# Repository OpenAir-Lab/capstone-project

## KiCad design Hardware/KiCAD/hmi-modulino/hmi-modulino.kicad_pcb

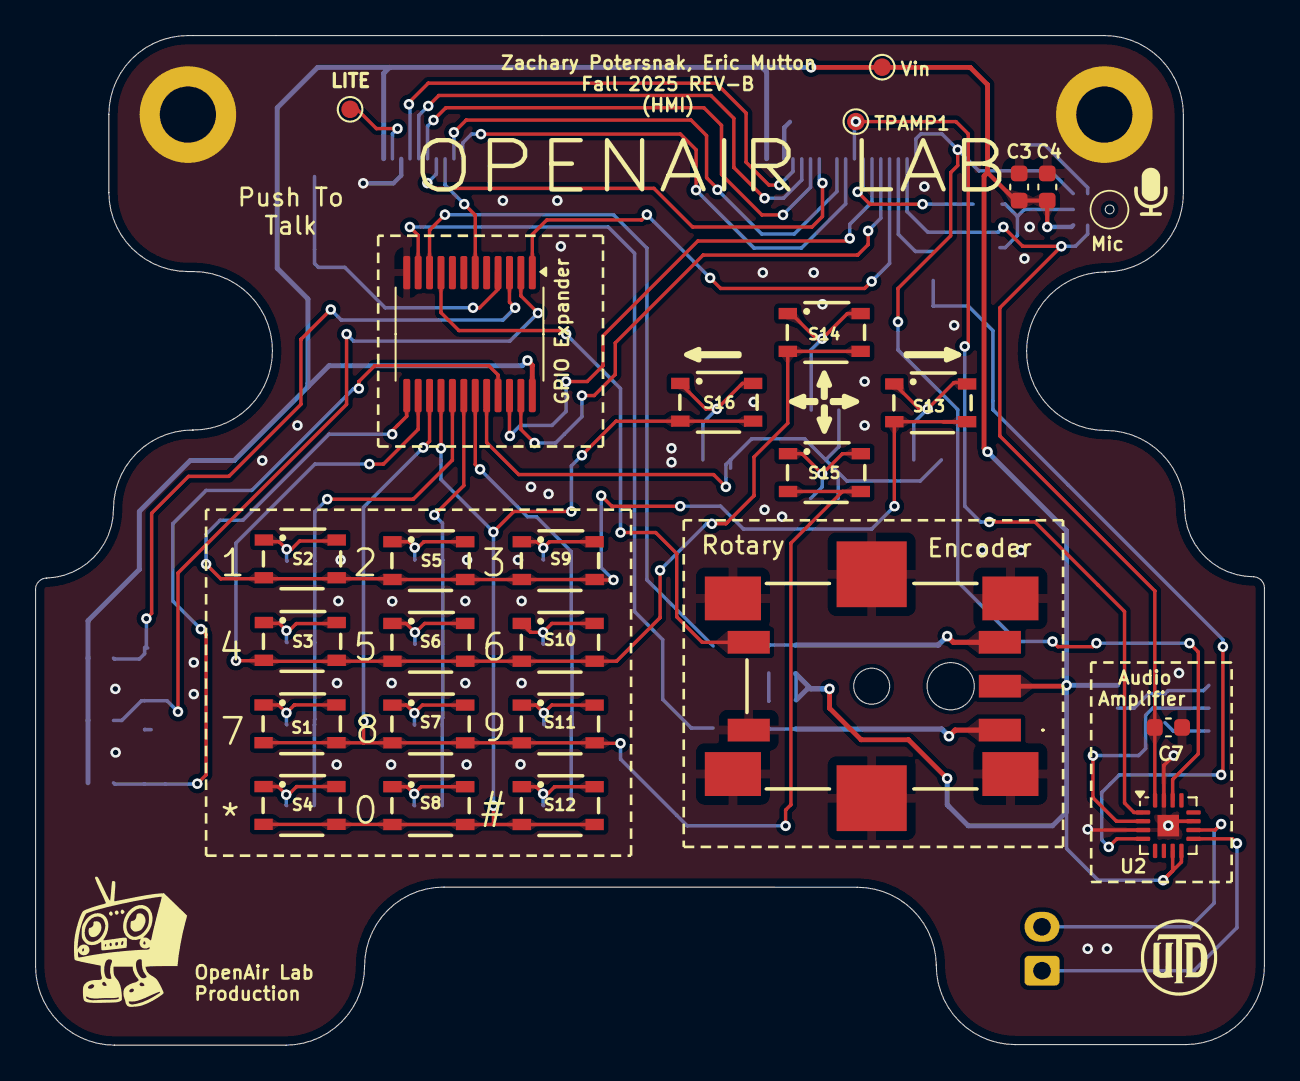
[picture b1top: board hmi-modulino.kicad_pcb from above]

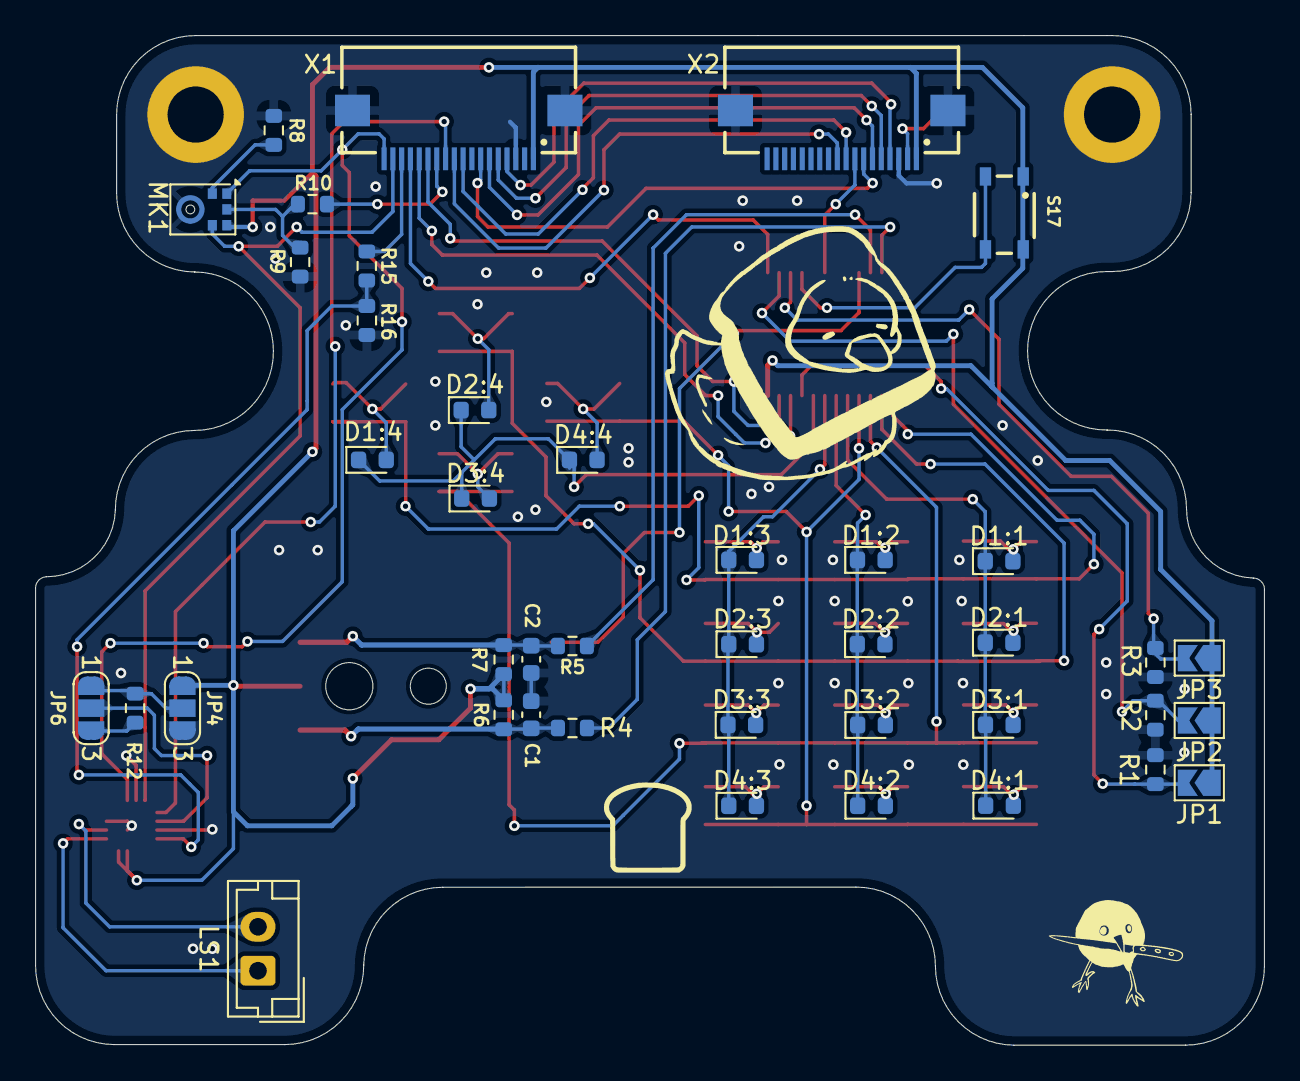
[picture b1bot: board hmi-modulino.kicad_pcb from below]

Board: 2 copper layers, 70.0 x 57.5 mm, 68 parts (41 on the bottom side), 58 nets.

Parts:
C1, C2: 0.01uF; C_0603_1608Metric
C3: 1uF; C_0603_1608Metric
C4: 0.1uF; C_0603_1608Metric
C7: 22pF; C_0603_1608Metric
D1:1, D1:2, D1:3, D1:4, D2:1, D2:2, D2:3, D2:4, D3:1, D3:2, D3:3, D3:4, D4:1, D4:2, D4:3, D4:4: D; D_0603_1608Metric
H1, H2: M3; MountingHole_3.2mm_M3_ISO14580_Pad
IC1: PCF8575PWR; SSOP-24_5.3x8.2mm_P0.65mm
JP1, JP2, JP3: SolderJumper_2_Open; SolderJumper-2_P1.3mm_Open_TrianglePad1.0x1.5mm
JP4: GAIN_{LOGIC}; SolderJumper-3_P1.3mm_Open_RoundedPad1.0x1.5mm_NumberLabels
JP6: GAIN_{R}; SolderJumper-3_P1.3mm_Open_RoundedPad1.0x1.5mm_NumberLabels
LS1: Speaker; JST_EH_B2B-EH-A_1x02_P2.50mm_Vertical
MK1: ICS-43434; InvenSense_ICS-43434-6_3.5x2.65mm
R1, R2, R3, R4, R5, R6, R7: 10k; R_0603_1608Metric
R8, R9: 47k; R_0603_1608Metric
R10: 68; R_0603_1608Metric
R12: 100k 5%; R_0603_1608Metric
R15: 2k; R_0603_1608Metric
R16: 100k; R_0603_1608Metric
S1, S2, S3, S4, S5, S6, S7, S8, S9, S10, S11, S12, S13, S14, S15, S16, S17: 434133025816
TP1: TestPoint; TestPoint_Pad_D1.0mm
TPAMP1: TestPoint_Pad_D1.0mm
U1: PEC11J-9215F-S0015; PEC11J9215FS0015
U2: MAX98357A; TQFN-16-1EP_3x3mm_P0.5mm_EP1.23x1.23mm
Vin: TestPoint; TestPoint_Pad_D1.0mm
X1, X2: EYESPI; Adafruit EYESPI FPC Connector

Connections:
+3.3V: C3.1, C4.1, IC1.24 (VCC), JP1.1 (A), JP2.1 (A), JP3.1 (A), JP4.1 (A), MK1.5 (VDD), R6.1, R7.2, S17.1, S17.2, U1.C1, U2.7 (VDD), U2.8 (VDD), Vin.1, X1.1, X2.1
/CARDCS: X1.10, X2.10
/Human-Machine Interface/AMP_DIN: TPAMP1.1, U2.1 (DIN), X1.11
/Human-Machine Interface/Audio/GAIN_SLOT: JP6.2 (C), U2.2 (GAIN_SLOT)
/Human-Machine Interface/Audio/~SD_MODE: R15.1, R16.2, U2.4 (~SD_MODE)
/Human-Machine Interface/BCLK: C7.1, MK1.4 (SCK), U2.16 (BCLK), X1.17
/Human-Machine Interface/ENC_CLK: IC1.11 (P7), R4.1
/Human-Machine Interface/ENC_DT: IC1.10 (P6), R5.1
/Human-Machine Interface/ENC_SW: IC1.9 (P5), U1.E1 (NO)
/Human-Machine Interface/Keypad/COL1: D1:1.1 (K), D2:1.1 (K), D3:1.1 (K), D4:1.1 (K), IC1.17 (P14)
/Human-Machine Interface/Keypad/COL2: D1:2.1 (K), D2:2.1 (K), D3:2.1 (K), D4:2.1 (K), IC1.18 (P15)
/Human-Machine Interface/Keypad/COL3: D1:3.1 (K), D2:3.1 (K), D3:3.1 (K), D4:3.1 (K), IC1.19 (P16)
/Human-Machine Interface/Keypad/COL4: D1:4.1 (K), D2:4.1 (K), D3:4.1 (K), D4:4.1 (K), IC1.20 (P17)
/Human-Machine Interface/Keypad/ROW1: IC1.13 (P10), S2.3, S2.4, S5.3, S5.4, S9.3, S9.4, S13.3, S13.4
/Human-Machine Interface/Keypad/ROW2: IC1.14 (P11), S3.3, S3.4, S6.3, S6.4, S10.3, S10.4, S14.3, S14.4
/Human-Machine Interface/Keypad/ROW3: IC1.15 (P12), S1.3, S1.4, S7.3, S7.4, S11.3, S11.4, S15.3, S15.4
/Human-Machine Interface/Keypad/ROW4: IC1.16 (P13), S4.3, S4.4, S8.3, S8.4, S12.3, S12.4, S16.3, S16.4
/Human-Machine Interface/LITE: TP1.1, X2.2
/Human-Machine Interface/LRCLK: MK1.1 (WS), U2.14 (LRCLK), X1.18
/Human-Machine Interface/MIC_DOUT: R10.2, X1.12
/Human-Machine Interface/PCF_A0: IC1.21 (A0), JP1.2 (B), R1.1
/Human-Machine Interface/PCF_A1: IC1.2 (A1), JP2.2 (B), R2.1
/Human-Machine Interface/PCF_A2: IC1.3 (A2), JP3.2 (B), R3.1
/Human-Machine Interface/TFTRST: IC1.6 (P2), X2.8
/Human-Machine Interface/~AMP_SD: R15.2, X1.16
/MISO: X1.6, X2.6
/MOSI: X1.5, X2.5
/SCK: X1.4, X2.4
/SCL: IC1.22 (SCL), X1.13
/SDA: IC1.23 (SDA), X1.14
/TFTCS: X1.9, X2.9
/TFTDC: X1.7, X2.7
GND: C1.2, C2.2, C3.2, C4.2, C7.2, H1.1, H2.1, IC1.12 (GND), JP4.3 (B), MK1.3 (GND), R1.2, R2.2, R3.2, R8.2, R9.2, R16.1, U1.D1 (COM), U1.MP1, U1.MP2, U1.MP3, U1.MP4, U1.MP5, U1.MP6, U2.3 (GND), U2.11 (GND), U2.15 (GND), U2.17 (PAD), X1.3, X1.Z1, X1.Z2, X2.3, X2.Z1, X2.Z2
unnamed: C1.1, R4.2, R6.2, U1.A1
unnamed: C2.1, R5.2, R7.1, U1.B1
unnamed: D1:1.2 (A), S2.1, S2.2
unnamed: D1:2.2 (A), S5.1, S5.2
unnamed: D1:3.2 (A), S9.1, S9.2
unnamed: D1:4.2 (A), S13.1, S13.2
unnamed: D2:1.2 (A), S3.1, S3.2
unnamed: D2:2.2 (A), S6.1, S6.2
unnamed: D2:3.2 (A), S10.1, S10.2
unnamed: D2:4.2 (A), S14.1, S14.2
unnamed: D3:1.2 (A), S1.1, S1.2
unnamed: D3:2.2 (A), S7.1, S7.2
unnamed: D3:3.2 (A), S11.1, S11.2
unnamed: D3:4.2 (A), S15.1, S15.2
unnamed: D4:1.2 (A), S4.1, S4.2
unnamed: D4:2.2 (A), S8.1, S8.2
unnamed: D4:3.2 (A), S12.1, S12.2
unnamed: D4:4.2 (A), S16.1, S16.2
unnamed: IC1.4 (P0), S17.3, S17.4
unnamed: JP4.2 (C), JP6.1 (A), R12.1
unnamed: JP6.3 (B), R12.2
unnamed: MK1.2 (LR), R8.1
unnamed: MK1.6 (SD), R9.1, R10.1
unnamed: LS1.2, U2.10 (OUTN)
unnamed: LS1.1, U2.9 (OUTP)

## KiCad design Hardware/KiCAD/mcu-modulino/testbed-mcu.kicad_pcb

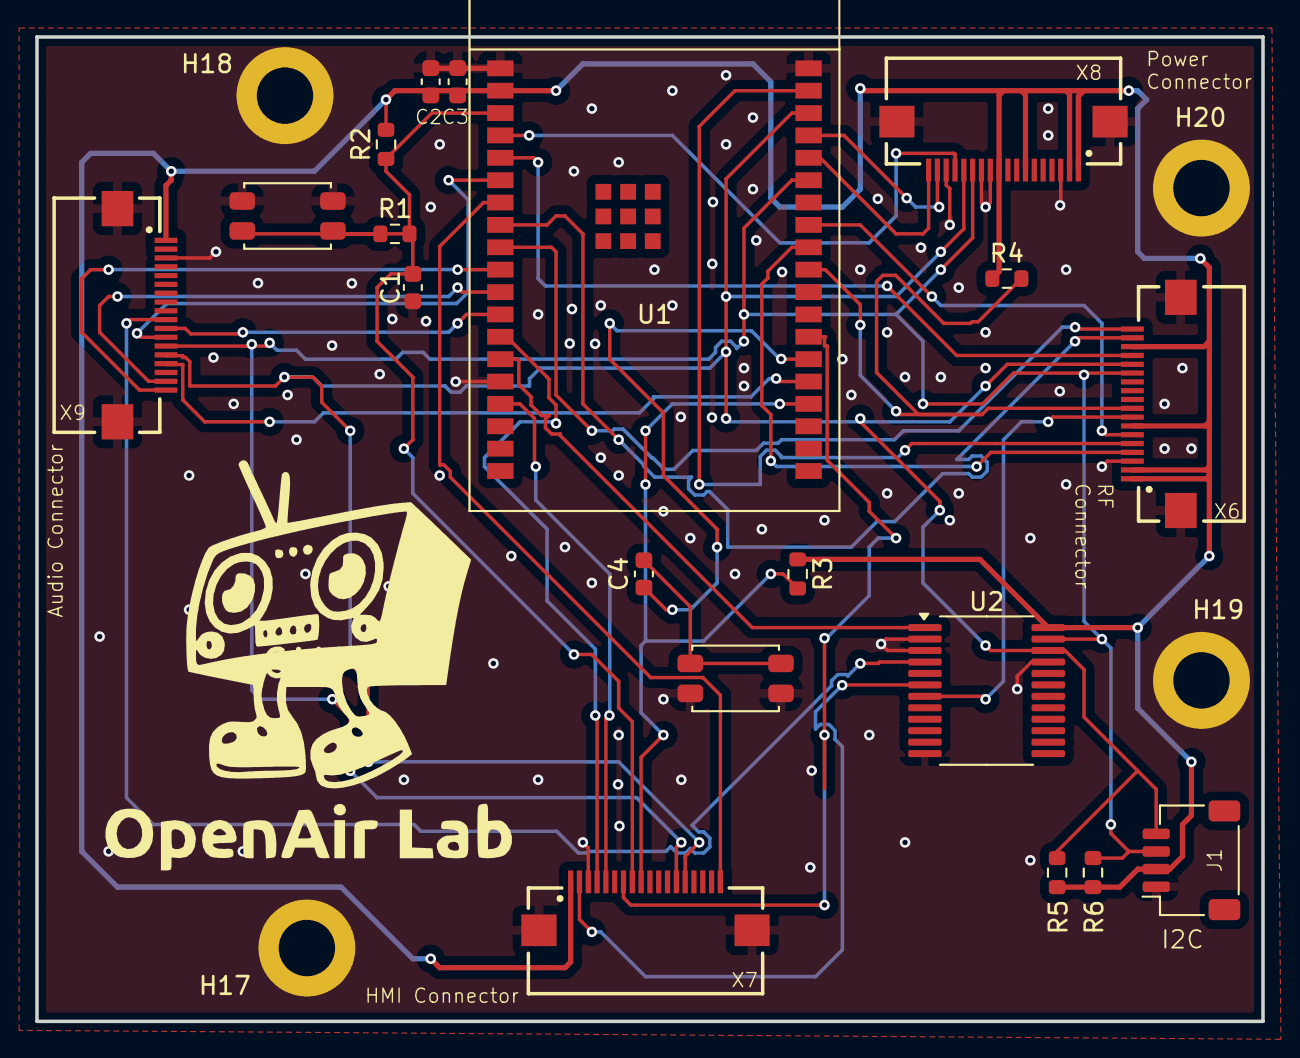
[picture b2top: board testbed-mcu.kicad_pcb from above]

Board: 2 copper layers, 69.6 x 55.9 mm, 23 parts (0 on the bottom side), 31 nets.

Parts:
C1, C3, C4: 0.1u; C_0603_1608Metric
C2: 10u; C_0603_1608Metric
H17, H18, H19, H20: MountingHole_Pad; MountingHole_3.2mm_M3_ISO14580_Pad
J1: Stemma QT; JST_SH_SM04B-SRSS-TB_1x04-1MP_P1.00mm_Horizontal
R1, R2, R3, R4: 10k; R_0603_1608Metric
R5, R6: 4.7k; R_0603_1608Metric
SW1, SW2: SW_Push; SW_SPST_EVQP2_MiddlePushTravel_H2.5mm
U1: ESP32-WROVER-E; ESP32-WROVER-IE
U2: PCF8575DBR; SSOP-24_5.3x8.2mm_P0.65mm
X6, X7, X8, X9: EYESPI; Adafruit EYESPI FPC Connector

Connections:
+3.3V: C2.2, C3.2, J1.2, R2.2, R3.1, R4.1, R5.1, R6.1, U1.2 (3V3), U2.24 (VCC), X6.1, X6.2, X6.7, X6.16, X7.1, X8.1, X8.2, X8.7, X8.10, X9.1
/AMP_SD: U2.4 (P0), X9.10
/CC1200_RST: U2.7 (P3), X6.8
/MCU/AUDIO_INT: U1.24 (IO2), X9.15
/MCU/BCLK: U1.11 (GPIO26), X9.17
/MCU/BMS_INT: U1.4 (GPIO36), X8.15
/MCU/DIN: U1.6 (GPIO34), X9.12
/MCU/DOUT: U1.12 (GPIO27), X9.11
/MCU/HMI_INT: U1.7 (GPIO35), X7.18
/MCU/HSPI_CS: R3.2, U1.23 (IO15), X7.9
/MCU/HSPI_DC: U1.26 (GPIO4), X7.7
/MCU/HSPI_MOSI: U1.16 (GPIO13), X7.5
/MCU/HSPI_SCLK: U1.13 (GPIO14), X7.4
/MCU/LRCLK: U1.10 (GPIO25), X9.18
/MCU/RF_INT: U1.5 (GPIO39), X6.15
/MCU/RX0: U1.34 (RXD0), X8.18
/MCU/TX0: U1.35 (TXD0), X8.17
/MCU/VSPI_CS: R4.2, U1.29 (IO5), X6.9
/MCU/VSPI_GDO0: U1.8 (GPIO32), X6.17
/MCU/VSPI_GDO2: U1.9 (GPIO33), X6.18
/MCU/VSPI_MISO: U1.31 (GPIO19), X6.6
/MCU/VSPI_MOSI: U1.37 (GPIO23), X6.5
/MCU/VSPI_SCLK: U1.30 (GPIO18), X6.4
/MCU/X_INT: U1.14 (IO12), U2.1 (~INT)
/TFT_BL_EN: U2.6 (P2), X7.2
EN: C1.2, R1.1, R1.2, R2.1, SW1.2, U1.3 (EN), X7.8
GND: C1.1, C2.1, C3.1, H17.1, H18.1, H19.1, H20.1, J1.1, SW1.1, SW2.2, U1.1 (GND), U1.15 (GND), U1.38 (GND), U2.2 (A1), U2.3 (A2), U2.12 (GND), U2.21 (A0), X6.3, X6.Z1, X6.Z2, X7.3, X7.Z1, X7.Z2, X8.3, X8.11, X8.12, X8.16, X8.Z1, X8.Z2, X9.3, X9.Z1, X9.Z2
unnamed: C4.2, SW2.1
unnamed: C4.1, U1.25 (IO0)
SCL: J1.4, R5.2, U1.36 (GPIO22), U2.22 (SCL), X6.14, X7.14, X8.14, X9.14
SDA: J1.3, R6.2, U1.33 (GPIO21), U2.23 (SDA), X6.13, X7.13, X8.13, X9.13

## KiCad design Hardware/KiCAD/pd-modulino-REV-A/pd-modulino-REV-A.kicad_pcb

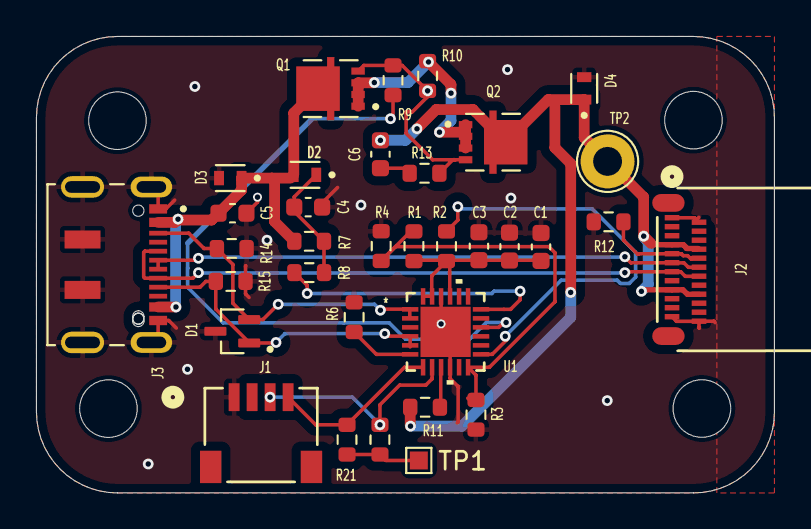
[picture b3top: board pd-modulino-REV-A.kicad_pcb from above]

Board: 2 copper layers, 41.0 x 25.4 mm, 34 parts (0 on the bottom side), 21 nets.

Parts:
C1, C2, C3, C4: 1.0u; C_0603_1608Metric
C5: 4.7u; C_0603_1608Metric
C6: 100n; C_0603_1608Metric
D1: ESDA25W; SOT65P210X110-3N
D2, D3, D4: ESDA25P35-1U1M; TVS_ESDA25P35-1U1M
J1: PRT-14417; CONN_PRT-14417_SPK
J2: USB4155-03-C; CONN_USB4155_GCT
J3: DX07S016JA1R1500; JAE_DX07S016JA1R1500
Q1, Q2: STL6P3LLH6; TRANS_STL6P3LLH6
R1, R2, R6: 10k; R_0603_1608Metric
R3, R4, R10: 100k; R_0603_1608Metric
R5, R21: 4.7k; R_0603_1608Metric
R7: 470; R_0603_1608Metric
R8, R11: 1k; R_0603_1608Metric
R9: 22k; R_0603_1608Metric
R12, R14, R15: 5.1k; R_0603_1608Metric
R13: 100; R_0603_1608Metric
TP1: TestPoint; TestPoint_Pad_1.0x1.0mm
TP2: TestPoint; TestPoint_Loop_D2.60mm_Drill1.6mm_Beaded
U1: STUSB4500QTR

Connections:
/Power Subsystem/2V7: C1.2, C2.2, C3.2, R1.2, R2.2, U1.21 (VREG_1V2), U1.23 (VREG_2V7), U1.24 (VDD)
/Power Subsystem/D+: J2.A6 (D+), J2.B7 (D+), J3.6 (D+), J3.7 (D+__1)
/Power Subsystem/D-: J2.A7 (D-), J2.B6 (D-), J3.5 (D-), J3.8 (D-__1)
/Power Subsystem/SCL: J1.4, R21.2, U1.7 (SCL)
/Power Subsystem/SDA: J1.3, R5.2, U1.8 (SDA)
/Power Subsystem/USB_CC1: D1.2, J3.3 (CC1), R14.1, U1.1 (CC1DB), U1.2 (CC1)
/Power Subsystem/USB_CC2: D1.1, J3.9 (CC2), R15.1, U1.4 (CC2), U1.5 (CC2DB)
/Power Subsystem/VBUS_VS_DISCH: R8.1, U1.18 (VBUS_VS_DISCH)
GND: C1.1, C2.1, C3.1, C4.2, C5.2, D1.3, D3.A, D4.A, J1.1, J2.A1 (GND), J2.A12 (GND), J2.B1 (GND), J2.B12 (GND), J3.1 (GND), J3.12 (GND__1), J3.S1 (SHIELD), J3.S2 (SHIELD__1), J3.S3 (SHIELD__2), J3.S4 (SHIELD__3), J3.S5 (SHIELD__4), J3.S6 (SHIELD__5), R3.1, R4.1, R6.1, R12.1, R14.2, R15.2, U1.10 (GND), U1.22 (VSYS), U1.25
unnamed: C4.1, D2.C, R7.1, R8.2
unnamed: C6.1, R13.1
unnamed: J2.A5 (CC1), J2.B8 (CC2), R12.2
unnamed: Q1.1, Q1.2, Q1.3, Q2.1, Q2.2, Q2.3, R10.2
unnamed: Q1.4, Q2.4, R9.2, R10.1, R13.2
unnamed: R5.1, R21.1, TP1.1
unnamed: R1.1, R3.2, R4.2, U1.12 (ADDR0)
unnamed: R2.1, U1.13 (ADDR1)
unnamed: R11.2, U1.9 (DISCH)
unnamed: R6.2, U1.6 (RESET)
unnamed: R9.1, U1.16 (VBUS_EN_SNK)
VBUS: C5.1, C6.2, D2.A, D3.C, D4.C, J2.A4 (VDD), J2.A9 (VDD), J2.B4 (VDD), J2.B9 (VDD), J3.2 (VBUS), J3.11 (VBUS__1), Q1.5_8, Q2.5_8, R7.2, R11.1, TP2.1

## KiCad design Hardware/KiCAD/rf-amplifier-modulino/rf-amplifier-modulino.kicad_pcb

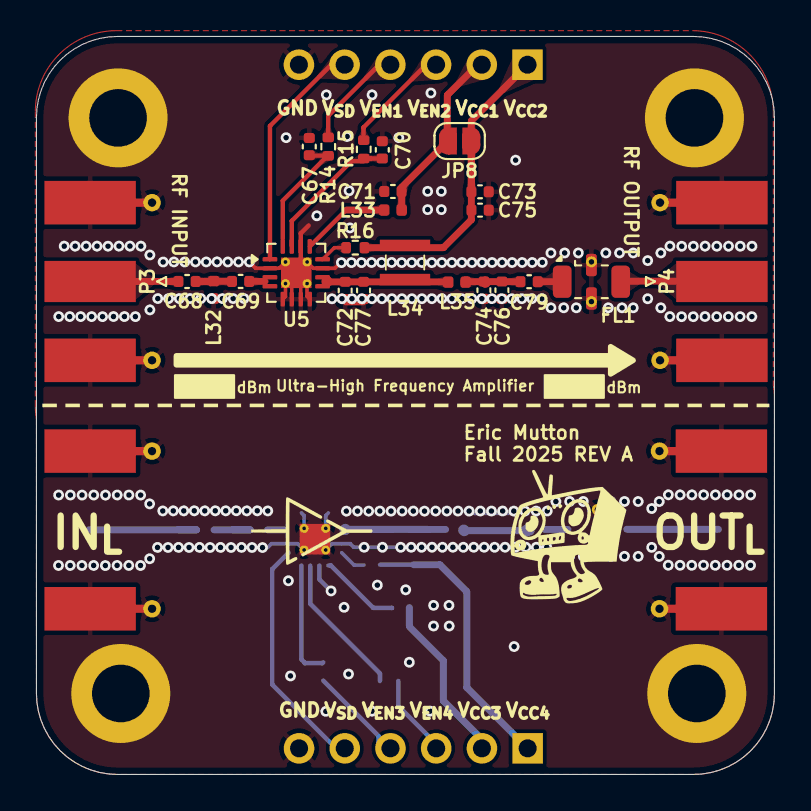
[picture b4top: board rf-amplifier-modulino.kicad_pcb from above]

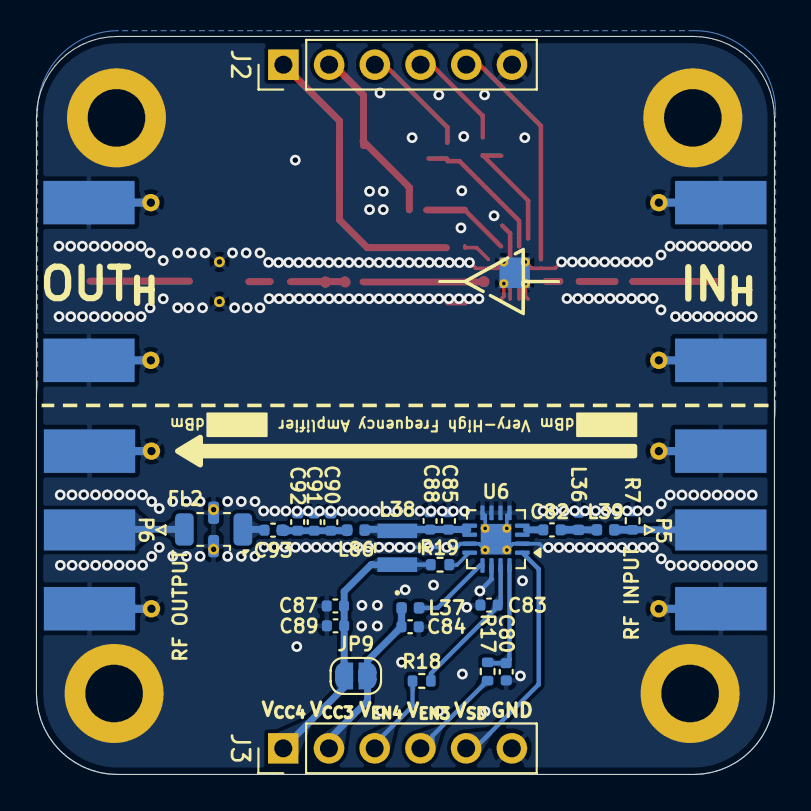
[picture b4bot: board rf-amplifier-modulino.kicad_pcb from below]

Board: 4 copper layers, 41.0 x 41.0 mm, 56 parts (28 on the bottom side), 32 nets.

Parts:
C67, C70, C75, C80, C83, C89: 1nF; C_0402_1005Metric
C68: 10pF; C_0402_1005Metric
C69, C72: 33pF; C_0402_1005Metric
C71: 0.1uF; C_0402_1005Metric
C73, C87: 10uF; C_0402_1005Metric
C74: 27pF; C_0402_1005Metric
C76: 3pF; C_0402_1005Metric
C77: 6.8pF; C_0402_1005Metric
C79, C88: 100pF; C_0402_1005Metric
C82, C93: 220pF; C_0402_1005Metric
C84: 1uF; C_0402_1005Metric
C85: 270pF; C_0402_1005Metric
C90, C91: 47pF; C_0402_1005Metric
C92: 18pF; C_0402_1005Metric
FL1: LFCN-490; Filter_Mini-Circuits_FV1206
FL2: LFCN-160; Filter_Mini-Circuits_FV1206
H1, H3, H4, H8: M3; MountingHole_3.2mm_M3_ISO14580_Pad
J2, J3: Conn_01x06_Pin; PinHeader_1x06_P2.54mm_Vertical
JP8, JP9: Single V_{CC}; SolderJumper-2_P1.3mm_Open_RoundedPad1.0x1.5mm
L32: 10nH; L_0402_1005Metric
L33: 20nH; L_0402_1005Metric
L34: 23nH; 0908SQ23NGLC
L35: 2.4nH; L_0402_1005Metric
L36: 150nH; L_0402_1005Metric
L37: 56nH; L_0402_1005Metric
L38: 1uH; IND_IMSC1008AZER_VIS
L39: 68nH; L_0402_1005Metric
L86: 9.1nH; L_0402_1005Metric
P3, P4, P5, P6: SMA; SMA_Molex_73251-1153_EdgeMount_Horizontal
R7: 350; R_0402_1005Metric
R14, R17: 1.27k; R_0402_1005Metric
R15, R18: 3.0k; R_0402_1005Metric
R16, R19: 0k; R_0402_1005Metric
U5, U6: GRF5604; QFN-16-1EP_3x3mm_P0.5mm_EP1.7x1.7mm_ThermalVias

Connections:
+3.3V: C71.1, C84.1, J2.2, J3.2, JP8.1 (A), JP9.1 (A), L33.1, L37.1
/RF Subsystem/RF Frontend/UHF 6W PA/RF_{IN}: C68.1, P3.1 (In)
/RF Subsystem/RF Frontend/UHF 6W PA/RF_{OUT}: C79.2, FL1.1 (IN)
/RF Subsystem/RF Frontend/UHF 6W PA/V_{CC2}: C73.1, C75.1, J2.1, JP8.2 (B), L34.1, R16.2
/RF Subsystem/RF Frontend/UHF 6W PA/V_{EN1}: C67.1, R14.1, U5.16 (V_{ENABLE1})
/RF Subsystem/RF Frontend/UHF 6W PA/V_{EN2}: C70.1, R15.1, U5.15 (V_{ENABLE2})
/RF Subsystem/RF Frontend/UHF 6W PA/V_{ENABLE1}: J2.4, R14.2
/RF Subsystem/RF Frontend/UHF 6W PA/V_{ENABLE2}: J2.3, R15.2
/RF Subsystem/RF Frontend/UHF 6W PA/V_{SHUTDOWN}: J2.5, U5.1 (V_{SHUTDOWN})
/RF Subsystem/RF Frontend/VHF 6W PA/RF_{IN}: L39.1, P5.1 (In), R7.2
/RF Subsystem/RF Frontend/VHF 6W PA/RF_{OUT}: C93.2, FL2.1 (IN)
/RF Subsystem/RF Frontend/VHF 6W PA/V_{CC2}: C87.1, C89.1, J3.1, JP9.2 (B), L38.1, R19.2
/RF Subsystem/RF Frontend/VHF 6W PA/V_{EN1}: C80.1, R17.1, U6.16 (V_{ENABLE1})
/RF Subsystem/RF Frontend/VHF 6W PA/V_{EN2}: C83.1, R18.1, U6.15 (V_{ENABLE2})
/RF Subsystem/RF Frontend/VHF 6W PA/V_{ENABLE1}: J3.4, R17.2
/RF Subsystem/RF Frontend/VHF 6W PA/V_{ENABLE2}: J3.3, R18.2
/RF Subsystem/RF Frontend/VHF 6W PA/V_{SHUTDOWN}: J3.5, U6.1 (V_{SHUTDOWN})
GND: C67.2, C70.2, C71.2, C72.2, C73.2, C74.2, C75.2, C76.2, C77.2, C80.2, C83.2, C84.2, C85.2, C87.2, C88.2, C89.2, C90.2, C91.2, C92.2, FL1.2 (GND), FL1.4 (GND), FL2.2 (GND), FL2.4 (GND), H1.1, H3.1, H4.1, H8.1, J2.6, J3.6, L32.2, L36.2, P3.2 (Ext), P4.2 (Ext), P5.2 (Ext), P6.2 (Ext), R7.1, U5.2 (GND/NC), U5.5 (GND/NC), U5.6 (GND/NC), U5.7 (GND/NC), U5.8 (GND/NC), U5.11 (GND/NC), U5.14 (GND/NC), U5.17 (PAD), U6.2 (GND/NC), U6.5 (GND/NC), U6.6 (GND/NC), U6.7 (GND/NC), U6.8 (GND/NC), U6.11 (GND/NC), U6.14 (GND/NC), U6.17 (PAD)
unnamed: C68.2, C69.1, L32.1
unnamed: C69.2, U5.3 (RF_{IN}), U5.4 (RF_{IN})
unnamed: C72.1, C77.1, L34.2, L35.1, U5.9 (RF_{OUT}), U5.10 (RF_{OUT})
unnamed: C74.1, C76.1, C79.1, L35.2
unnamed: C82.1, L36.1, L39.2
unnamed: C82.2, U6.3 (RF_{IN}), U6.4 (RF_{IN})
unnamed: C85.1, C88.1, L38.2, L86.1, U6.9 (RF_{OUT}), U6.10 (RF_{OUT})
unnamed: C90.1, C91.1, C92.1, C93.1, L86.2
unnamed: FL1.3 (OUT), P4.1 (In)
unnamed: FL2.3 (OUT), P6.1 (In)
unnamed: R16.1, U5.12 (V_{BIAS})
unnamed: L33.2, U5.13 (V_{CC1})
unnamed: R19.1, U6.12 (V_{BIAS})
unnamed: L37.2, U6.13 (V_{CC1})

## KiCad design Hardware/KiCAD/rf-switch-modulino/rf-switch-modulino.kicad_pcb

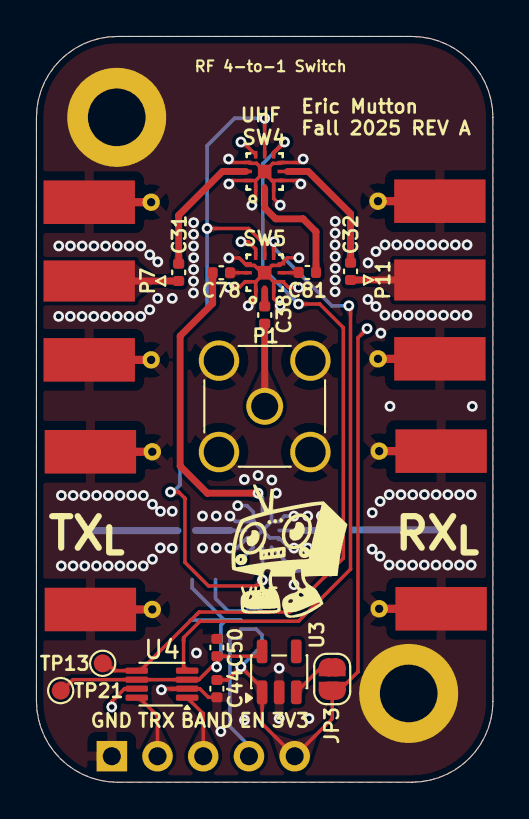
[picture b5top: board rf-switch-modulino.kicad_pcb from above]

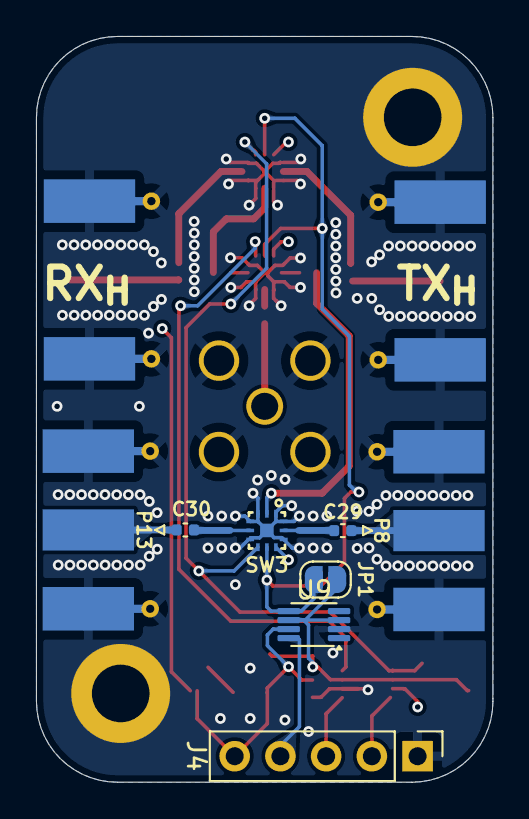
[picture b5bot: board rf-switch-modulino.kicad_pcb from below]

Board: 4 copper layers, 25.4 x 41.4 mm, 27 parts (8 on the bottom side), 24 nets.

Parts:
C29, C30, C31, C32, C78, C81: 1nF; C_0402_1005Metric
C38: 100pF; C_0402_1005Metric
C44, C50: 1uF; C_0402_1005Metric
H5, H6: M3; MountingHole_3.2mm_M3_ISO14580_Pad
J4: RF Switch; PinHeader_1x05_P2.54mm_Vertical
JP1, JP3: EN; SolderJumper-2_P1.3mm_Open_RoundedPad1.0x1.5mm
P1: SMA; SMA_Amphenol_901-144_Vertical
P7, P8, P11, P13: SMA; SMA_Molex_73251-1153_EdgeMount_Horizontal
SW3, SW4, SW5: SKY13330-397LF
TP13: TRX_SW_{+2.5V}; TestPoint_Pad_D1.0mm
TP21: +2.5V; TestPoint_Pad_D1.0mm
U3: LP5907MFX-2.5; SOT-23-5
U4, U9: TXS0101DBV; VSSOP-8_2.3x2mm_P0.5mm

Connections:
+2.5V: C50.2, JP1.1 (A), TP21.1, U3.5 (OUT), U4.3 (VCCA), U4.6 (OE), U9.3 (VCCA), U9.6 (OE)
+3.3V: C44.2, J4.5, JP3.1 (A), SW3.9 (VDD), SW4.9 (VDD), SW5.9 (VDD), U3.1 (IN), U4.7 (VCCB), U9.7 (VCCB)
/RF Subsystem/EN_{BAND}: JP1.2 (B), SW3.8 (EN), SW4.8 (EN), SW5.8 (EN), U9.5 (A1)
/RF Subsystem/RF Frontend/RX_{UHF}: C32.1, P11.1 (In)
/RF Subsystem/RF Frontend/RX_{VHF}: C30.1, P13.1 (In)
/RF Subsystem/RF Frontend/TX_{UHF}: C31.1, P7.1 (In)
/RF Subsystem/RF Frontend/TX_{VHF}: C29.1, P8.1 (In)
/RF Subsystem/RFSW_{BAND}: J4.3, U4.1 (B2)
/RF Subsystem/RFSW_{EN}: J4.4, U9.8 (B1)
/RF Subsystem/RFSW_{TRX}: J4.2, U4.8 (B1)
/RF Subsystem/SW_BAND: SW5.7 (CTRL), U4.4 (A2)
/RF Subsystem/SW_TRX: SW3.7 (CTRL), SW4.7 (CTRL), TP13.1, U4.5 (A1)
GND: C44.1, C50.1, H5.1, H6.1, J4.1, P1.2 (Ext), P7.2 (Ext), P8.2 (Ext), P11.2 (Ext), P13.2 (Ext), SW3.1 (GND), SW3.3 (GND), SW3.4 (GND), SW3.6 (GND), SW3.10 (GND), SW3.12 (GND), SW3.13 (GND), SW4.1 (GND), SW4.3 (GND), SW4.4 (GND), SW4.6 (GND), SW4.10 (GND), SW4.12 (GND), SW4.13 (GND), SW5.1 (GND), SW5.3 (GND), SW5.4 (GND), SW5.6 (GND), SW5.10 (GND), SW5.12 (GND), SW5.13 (GND), U3.2 (GND), U4.2 (GND), U9.2 (GND)
unnamed: JP3.2 (B), U3.3 (EN)
unnamed: C38.1, P1.1 (In)
unnamed: C78.1, SW3.2 (RF1_COM)
unnamed: C29.2, SW3.11 (RF2)
unnamed: C30.2, SW3.5 (RF3)
unnamed: C81.1, SW4.2 (RF1_COM)
unnamed: C31.2, SW4.11 (RF2)
unnamed: C32.2, SW4.5 (RF3)
unnamed: C38.2, SW5.2 (RF1_COM)
unnamed: C78.2, SW5.11 (RF2)
unnamed: C81.2, SW5.5 (RF3)

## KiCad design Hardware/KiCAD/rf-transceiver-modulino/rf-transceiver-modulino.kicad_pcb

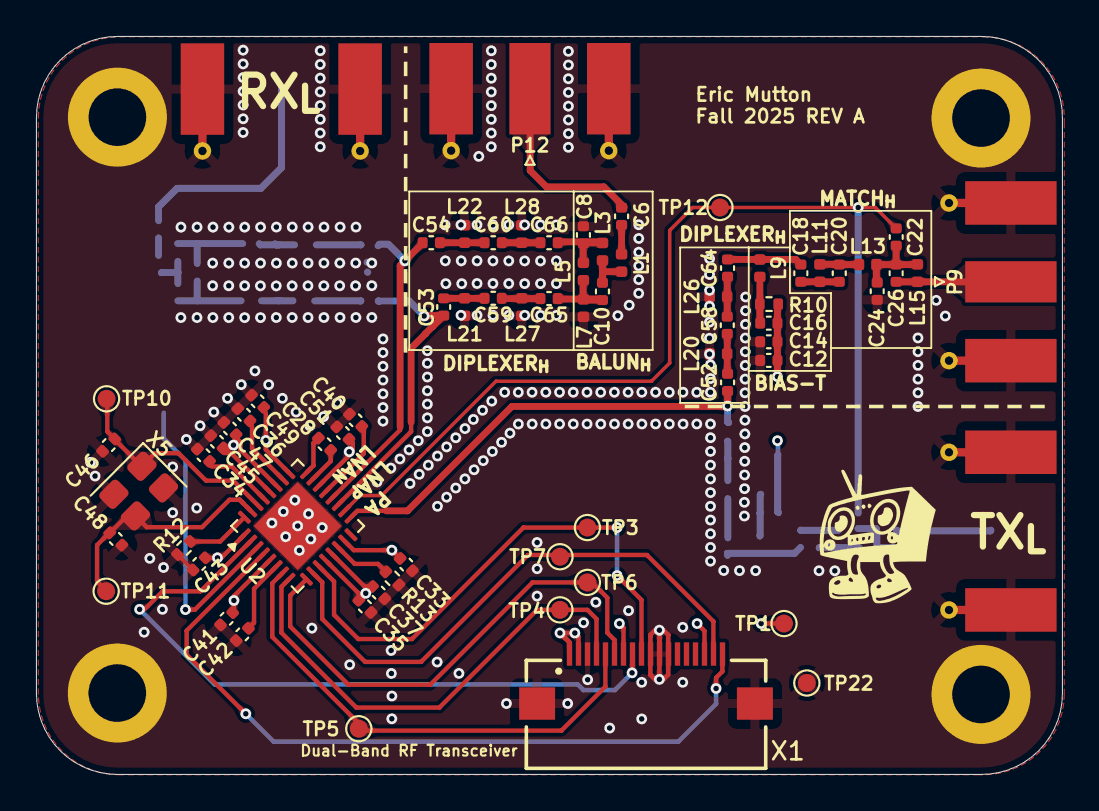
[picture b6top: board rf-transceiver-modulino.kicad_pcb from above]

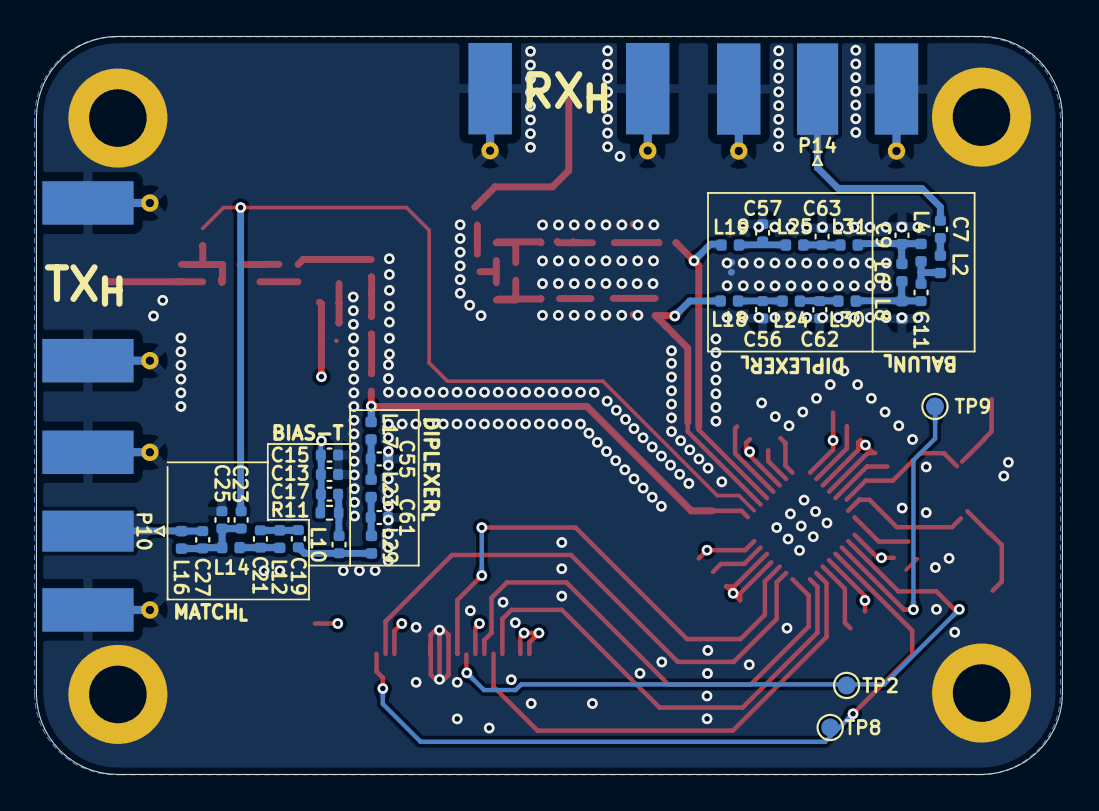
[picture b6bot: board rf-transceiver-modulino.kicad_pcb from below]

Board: 4 copper layers, 57.0 x 41.0 mm, 112 parts (40 on the bottom side), 58 nets.

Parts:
C6, C8, C10: 5.1pF; C_0402_1005Metric
C7, C9, C11, C21, C23: 12pF; C_0402_1005Metric
C12: 100p; C_0402_1005Metric
C13, C17: 100pF; C_0402_1005Metric
C14, C40: 10n; C_0402_1005Metric
C15: 10nF; C_0402_1005Metric
C16: 56p; C_0402_1005Metric
C18: 39p; C_0402_1005Metric
C19: 82pF; C_0402_1005Metric
C20: 2.2p; C_0402_1005Metric
C22: 1nF; C_0402_1005Metric
C24: 6.2p; C_0402_1005Metric
C25: 15pF; C_0402_1005Metric
C26, C27: 1.2p; C_0402_1005Metric
C28: 1.5n; C_0402_1005Metric
C33, C34, C35, C36, C37, C41, C43, C45, C47, C49, C51: 47n; C_0402_1005Metric
C42: 220n; C_0402_1005Metric
C46, C48: 15p; C_0402_1005Metric
C52, C53, C54, C64, C65, C66: 4.7pF; C_0402_1005Metric
C55, C56, C57, C61, C62, C63: 18pF; C_0402_1005Metric
C58, C59, C60: 2.7pF; C_0402_1005Metric
H1, H2, H3, H5: M3; MountingHole_3.2mm_M3_ISO14580_Pad
L1, L20, L21, L22, L26, L27, L28: 15nH; L_0402_1005Metric
L2: 39nH; L_0402_1005Metric
L3, L7: 27nH; L_0402_1005Metric
L4, L8: 82nH; L_0402_1005Metric
L5, L9: 56n; L_0402_1005Metric
L6: 150n; L_0402_1005Metric
L10: 220nH; C_0402_1005Metric
L11: 15n; L_0402_1005Metric
L12: 18nH; L_0402_1005Metric
L13: 43n; L_0402_1005Metric
L14, L23, L24, L25: 100nH; L_0402_1005Metric
L15: 22n; L_0402_1005Metric
L16, L17, L18, L19, L29, L30, L31: 68nH; L_0402_1005Metric
P9, P10, P12, P14: SMA; SMA_Molex_73251-1153_EdgeMount_Horizontal
R10: 18; R_0402_1005Metric
R11: 22; R_0402_1005Metric
R12: 0R; R_0402_1005Metric
R13: 56k; R_0402_1005Metric
TP1: +3.3V; TestPoint_Pad_D1.0mm
TP2: NRST; TestPoint_Pad_D1.0mm
TP3: NCS; TestPoint_Pad_D1.0mm
TP4: SCLK; TestPoint_Pad_D1.0mm
TP5: MOSI; TestPoint_Pad_D1.0mm
TP6: IO1/MISO; TestPoint_Pad_D1.0mm
TP7: IO0; TestPoint_Pad_D1.0mm
TP8: IO2; TestPoint_Pad_D1.0mm
TP9: IO3; TestPoint_Pad_D1.0mm
TP10: X1; TestPoint_Pad_D1.0mm
TP11: X2; TestPoint_Pad_D1.0mm
TP12: TRX_SW; TestPoint_Pad_D1.0mm
TP22: GND; TestPoint_Pad_D1.0mm
U2: CC1200RHBR; QFN-32-1EP_5x5mm_P0.5mm_EP3.45x3.45mm
X1: EYESPI; Adafruit EYESPI FPC Connector
X5: 40 MHz; Crystal_SMD_3225-4Pin_3.2x2.5mm

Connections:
+3.3V: C12.1, C13.1, C14.1, C15.1, C16.1, C17.1, C33.1, C35.1, C37.1, C41.1, C43.1, C45.1, C47.1, C49.1, C51.1, R10.1, R11.1, TP1.1, U2.1 (VDD_GUARD), U2.5 (DVDD), U2.12 (DVDD), U2.13 (AVDD_IF), U2.15 (AVDD_RF), U2.22 (AVDD_SYNTH1), U2.25 (AVDD_PFD_CHP), U2.27 (AVDD_SYNTH2), U2.28 (AVDD_XOSC), X1.1, X1.2, X1.7, X1.16
/RF Subsystem/LNA_N: C54.1, L19.1, U2.20 (LNA_N)
/RF Subsystem/LNA_N_{UHF}: C8.1, C66.2, L3.1, L5.2
/RF Subsystem/LNA_N_{VHF}: C9.1, L4.1, L6.2, L31.2
/RF Subsystem/LNA_P: C53.1, L18.1, U2.19 (LNA_P)
/RF Subsystem/LNA_P_{UHF}: C10.1, C65.2, L5.1, L7.1
/RF Subsystem/LNA_P_{VHF}: C11.1, L6.1, L8.1, L30.1
/RF Subsystem/PA_{SHUTDOWN}: TP9.1, U2.3 (GPIO3)
/RF Subsystem/PA_{UHF}: C18.2, C64.2, L9.2
/RF Subsystem/PA_{VHF}: C19.2, L10.2, L29.2
/RF Subsystem/TRX_GPIO0: TP7.1, U2.10 (GPIO0), X1.17
/RF Subsystem/TRX_GPIO2: TP8.1, U2.4 (GPIO2), X1.18
/RF Subsystem/TRX_MISO: TP6.1, U2.9 (SO(GPIO1)), X1.6
/RF Subsystem/TRX_MOSI: TP5.1, U2.7 (SI), X1.5
/RF Subsystem/TRX_NCS: TP3.1, U2.11 (~CS), X1.9
/RF Subsystem/TRX_NRST: TP2.1, U2.2 (~RESET), X1.8
/RF Subsystem/TRX_PA: C52.1, L17.1, U2.17 (PA)
/RF Subsystem/TRX_SCLK: TP4.1, U2.8 (SCLK), X1.4
/RF Subsystem/TRX_X1: C46.2, TP10.1, U2.30 (XOSC_Q1), X5.1
/RF Subsystem/TRX_X2: C48.1, TP11.1, U2.31 (XOSC_Q2), X5.3
/RF Subsystem/TRX_{SW}: C22.1, C23.1, TP12.1, U2.18 (TRX_SW)
GND: C8.2, C9.2, C12.2, C13.2, C14.2, C15.2, C24.2, C25.2, C33.2, C34.2, C35.2, C36.2, C37.2, C40.2, C41.2, C42.2, C43.2, C45.2, C46.1, C47.2, C48.2, C49.2, C51.2, C55.2, C56.2, C57.2, C61.2, C62.2, C63.2, H1.1, H2.1, H3.1, H5.1, L7.2, L8.2, L20.2, L21.2, L22.2, L26.2, L27.2, L28.2, P9.2 (Ext), P10.2 (Ext), P12.2 (Ext), P14.2 (Ext), R12.1, R13.2, TP22.1, U2.33 (GND_EP), X1.3, X1.10, X1.11, X1.12, X1.Z1, X1.Z2, X5.2, X5.4
unnamed: C6.2, L1.1
unnamed: C7.2, L2.1
unnamed: C10.2, L1.2, L3.2
unnamed: C11.2, L2.2, L4.2
unnamed: C16.2, L9.1, R10.2
unnamed: C17.2, L10.1, R11.2
unnamed: C18.1, C20.2, L11.1
unnamed: C19.1, C21.2, L12.1
unnamed: C20.1, L11.2, L13.1
unnamed: C21.1, L12.2, L14.1
unnamed: C22.2, C24.1, C26.1, L13.2, L15.1
unnamed: C23.2, C25.1, C27.1, L14.2, L16.1
unnamed: C52.2, C58.1, L20.1
unnamed: C53.2, C59.1, L21.1
unnamed: C54.2, C60.1, L22.1
unnamed: C55.1, L17.2, L23.1
unnamed: C56.1, L18.2, L24.1
unnamed: C57.1, L19.2, L25.1
unnamed: C58.2, C64.1, L26.1
unnamed: C59.2, C65.1, L27.1
unnamed: C60.2, C66.1, L28.1
unnamed: C61.1, L23.2, L29.1
unnamed: C62.1, L24.2, L30.2
unnamed: C63.1, L25.2, L31.1
unnamed: C26.2, L15.2, P9.1 (In)
unnamed: C27.2, L16.2, P10.1 (In)
unnamed: C6.1, P12.1 (In)
unnamed: C7.1, P14.1 (In)
unnamed: C42.1, U2.6 (DCPL)
unnamed: C36.1, U2.26 (DCPL_PFD_CHP)
unnamed: C40.1, U2.21 (DCPL_VCO)
unnamed: C34.1, U2.29 (DCPL_XOSC)
unnamed: R12.2, U2.32 (EXT_XOSC)
unnamed: C28.2, U2.23 (LPF0)
unnamed: C28.1, U2.24 (LPF1)
unnamed: R13.1, U2.14 (RBIAS)
